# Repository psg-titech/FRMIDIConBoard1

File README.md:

# FRMIDIConBoard1
Functional Reactive MIDI Controller Board #1

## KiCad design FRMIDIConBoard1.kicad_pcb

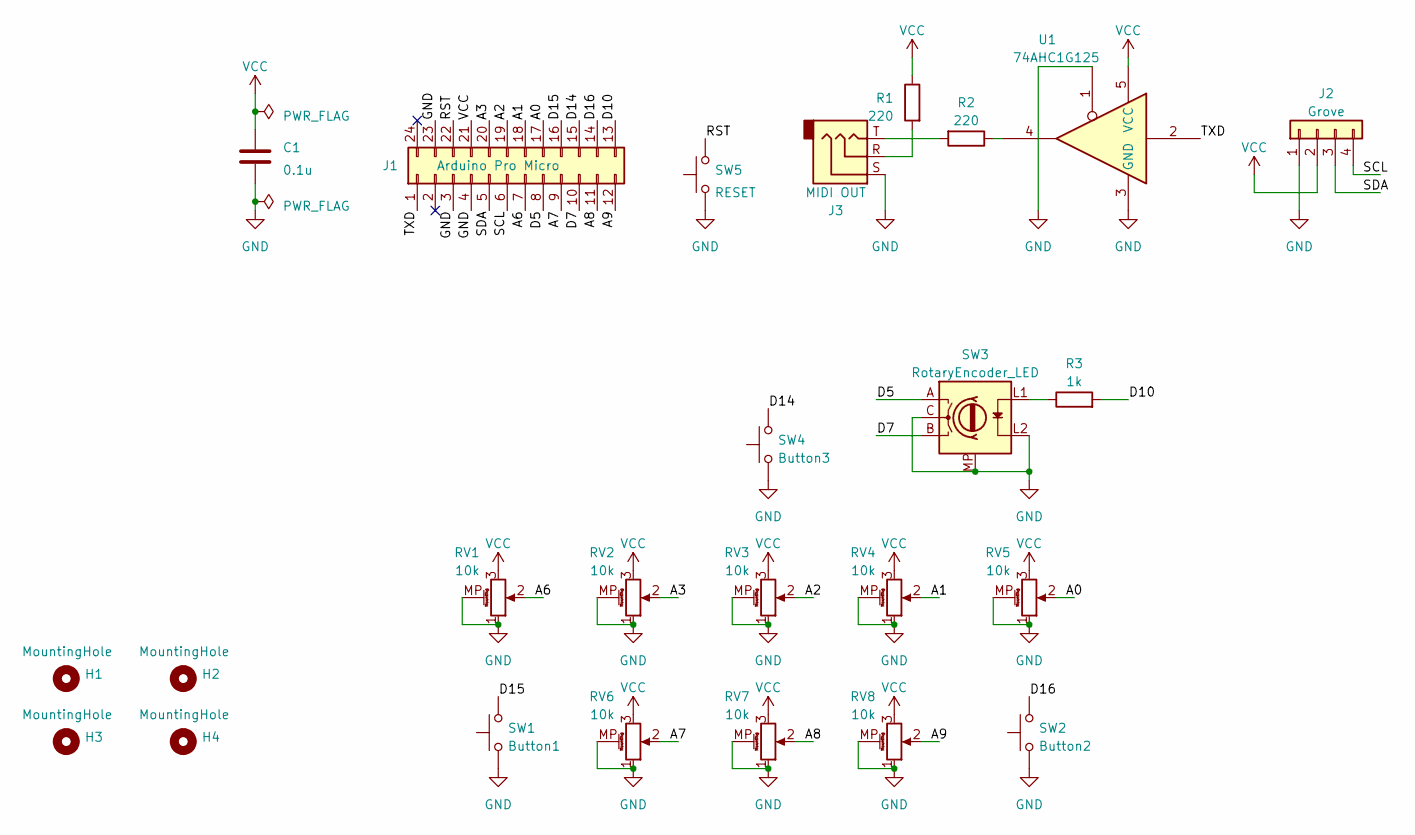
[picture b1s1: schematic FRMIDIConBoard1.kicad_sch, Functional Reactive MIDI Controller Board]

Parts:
C1: 0.1u; C_0805_2012Metric_Pad1.18x1.45mm_HandSolder
H1, H2, H3, H4: MountingHole; MountingHole_3.2mm_M3_ISO14580
J1: Arduino Pro Micro; DIP-24_W15.24mm_Socket_LongPads
J2: Grove; NS-Tech_Grove_1x04_P2mm_Vertical
J3: MIDI OUT; Jack_3.5mm_Switronic_ST-005-G_horizontal
R1, R2: 220; R_0805_2012Metric_Pad1.20x1.40mm_HandSolder
R3: 1k; R_0805_2012Metric_Pad1.20x1.40mm_HandSolder
RV1, RV2, RV3, RV4, RV5, RV6, RV7, RV8: 10k; Potentiometer_Alps_RK09K_Single_Vertical
SW1: Button1; SW_PUSH-12mm
SW2: Button2; SW_PUSH-12mm
SW3: RotaryEncoder_LED; RotaryEncoder_TopUp_EC12PL-LED_Vertical_H20mm_CircularMount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
SW4: Button3; SW_PUSH_6mm_H5mm
SW5: RESET; SW_Push_SPST_NO_Alps_SKRK
U1: 74AHC1G125; SOT-23-5_HandSoldering

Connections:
/A0: J1.17, RV5.2
/A1: J1.18, RV4.2
/A2: J1.19, RV3.2
/A3: J1.20, RV2.2
/A6: J1.7, RV1.2
/A7: J1.9, RV6.2
/A8: J1.11, RV7.2
/A9: J1.12, RV8.2
/D5: J1.8, SW3.A
/D7: J1.10, SW3.B
/D10: J1.13, R3.2
/D14: J1.15, SW4.2
/D15: J1.16, SW1.2
/D16: J1.14, SW2.2
/RST: J1.22, SW5.2
/SCL: J1.6, J2.4
/SDA: J1.5, J2.3
/TXD: J1.1, U1.2
GND: C1.2, J1.3, J1.4, J1.23, J2.1, J3.S, RV1.1, RV1.MP (MountPin), RV2.1, RV2.MP (MountPin), RV3.1, RV3.MP (MountPin), RV4.1, RV4.MP (MountPin), RV5.1, RV5.MP (MountPin), RV6.1, RV6.MP (MountPin), RV7.1, RV7.MP (MountPin), RV8.1, RV8.MP (MountPin), SW1.1, SW2.1, SW3.C, SW3.L2, SW3.MP, SW4.1, SW5.1, U1.1, U1.3 (GND)
unnamed: J3.R, R1.2
unnamed: J3.T, R2.2
unnamed: R2.1, U1.4
unnamed: R3.1, SW3.L1
VCC: C1.1, J1.21, J2.2, R1.1, RV1.3, RV2.3, RV3.3, RV4.3, RV5.3, RV6.3, RV7.3, RV8.3, U1.5 (VCC)

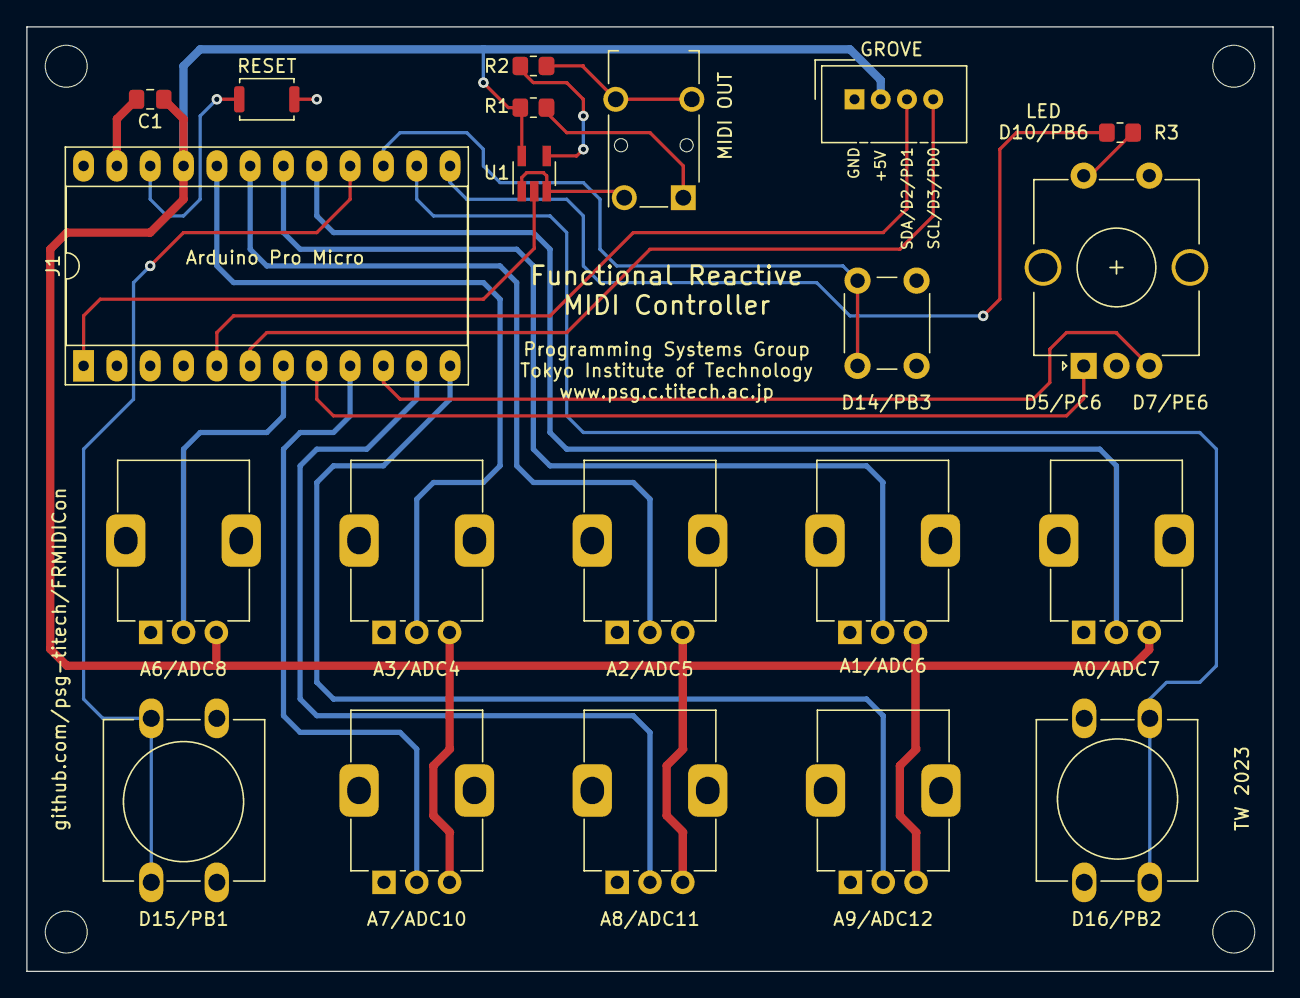
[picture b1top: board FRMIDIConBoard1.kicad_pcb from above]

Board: 2 copper layers, 95.0 x 72.0 mm, 25 parts (0 on the bottom side), 24 nets.

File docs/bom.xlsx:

ID | Description | Model | Manufacturer | PCS | Manufacturer URL | Shop URL1 | Shop URL2
U1 | Single Buffer Gate | 74AHC1G125W5 | Diodes Incorporated | 1 |  | https://akizukidenshi.com/catalog/g/gI-17605/
C1 | Ceramic Capasitor 0.1u SMD 2012 | TMK212F104ZQ-T | Taiyo Yuden | 1 |  | https://akizukidenshi.com/catalog/g/gP-17818/
R1, R2 | Resistor 220ohm SMD 2012 | RK73B2ATTD221J | KOA | 2 | https://www.koaglobal.com/~/media/Files/KOA_Global/EN/produc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 | https://www.sengoku.co.jp/mod/sgk_cart/detail.php?code=EEHD-57BH
R3 | Resistor 470ohm SMD 2012 | RK73B2ATTD471J | KOA | 1 | https://www.koaglobal.com/~/media/Files/KOA_Global/EN/produc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 | https://www.sengoku.co.jp/mod/sgk_cart/detail.php?code=EEHD-57BS
SW1, SW2 | Tactical Switch 12mm TH | TVGP01-G73BB | Zhejiang Jianfu Electronics | 2 |  | https://akizukidenshi.com/catalog/g/gP-09826/ | https://www.amazon.co.jp/gp/product/B07J66NDTR
SW3 | Rotary Encoder with LED | EC12PLRVF-D-24K-24-24C-02/06-6 | Top-Up Industry Corporation | 1 |  | https://akizukidenshi.com/catalog/g/gP-05762/
SW4 | Tactical Switch 6mm TH | DTS-63-F-N-V-RED | Cosland Co,. Ltd. | 1 |  | https://akizukidenshi.com/catalog/g/gP-03646/
SW5 | Tactical Switch 6mm SMD | TVAF06-A020B-R | Zhejiang Jianfu Electronics | 1 |  | https://akizukidenshi.com/catalog/g/gP-14888/
RV1-8 | Rotary Potentiometer 10KB | RK09K1130A5R | Alps Alpine | 8 | https://tech.alpsalpine.com/j/products/detail/RK09K1130A5R/ | https://www.zaikostore.com/zaikostore/stockDetail?productNam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 | https://www.amazon.co.jp/gp/product/B07TFTK41V
J1 | IC Socket 24P 600mil | 2227MC-24-06 | Neltron Industrial | 1 |  | https://akizukidenshi.com/catalog/g/gP-00032/
J2 | Grove Female Header 4pin/2mm TH | SKU110990030 | Seeed Studio | 1 | https://www.seeedstudio.com/Grove-Universal-4-pin-connector.html | https://www.switch-science.com/products/1122 | https://www.sengoku.co.jp/mod/sgk_cart/detail.php?code=EEHD-4KKK | https://www.marutsu.co.jp/pc/i/829425/
J3 | 3.5mm Phone Jack | ST-005-G | Switronic lndustrial Corp. | 1 |  | https://akizukidenshi.com/catalog/g/gC-02460/
 | Microcontroller Board | Pro Micro 5V/16MHz | Sparkfun | 1 | https://www.sparkfun.com/products/12640 | https://www.switch-science.com/products/1623
 | IC Connector 2.54mm 1x40 | 6604P-40G-121 | Neltron Industrial | 1 |  | https://akizukidenshi.com/catalog/g/gP-01382/

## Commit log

2023-05-14 Added test1
2023-05-16 Modified ADC prescaling factor
2023-05-17 Added Test Program for NTS-1
